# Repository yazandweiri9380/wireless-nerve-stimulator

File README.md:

# wireless-nerve-stimulator
Hardware designs, firmware, and supporting software for a compact wireless peripheral nerve stimulator with onboard inverse mapping.

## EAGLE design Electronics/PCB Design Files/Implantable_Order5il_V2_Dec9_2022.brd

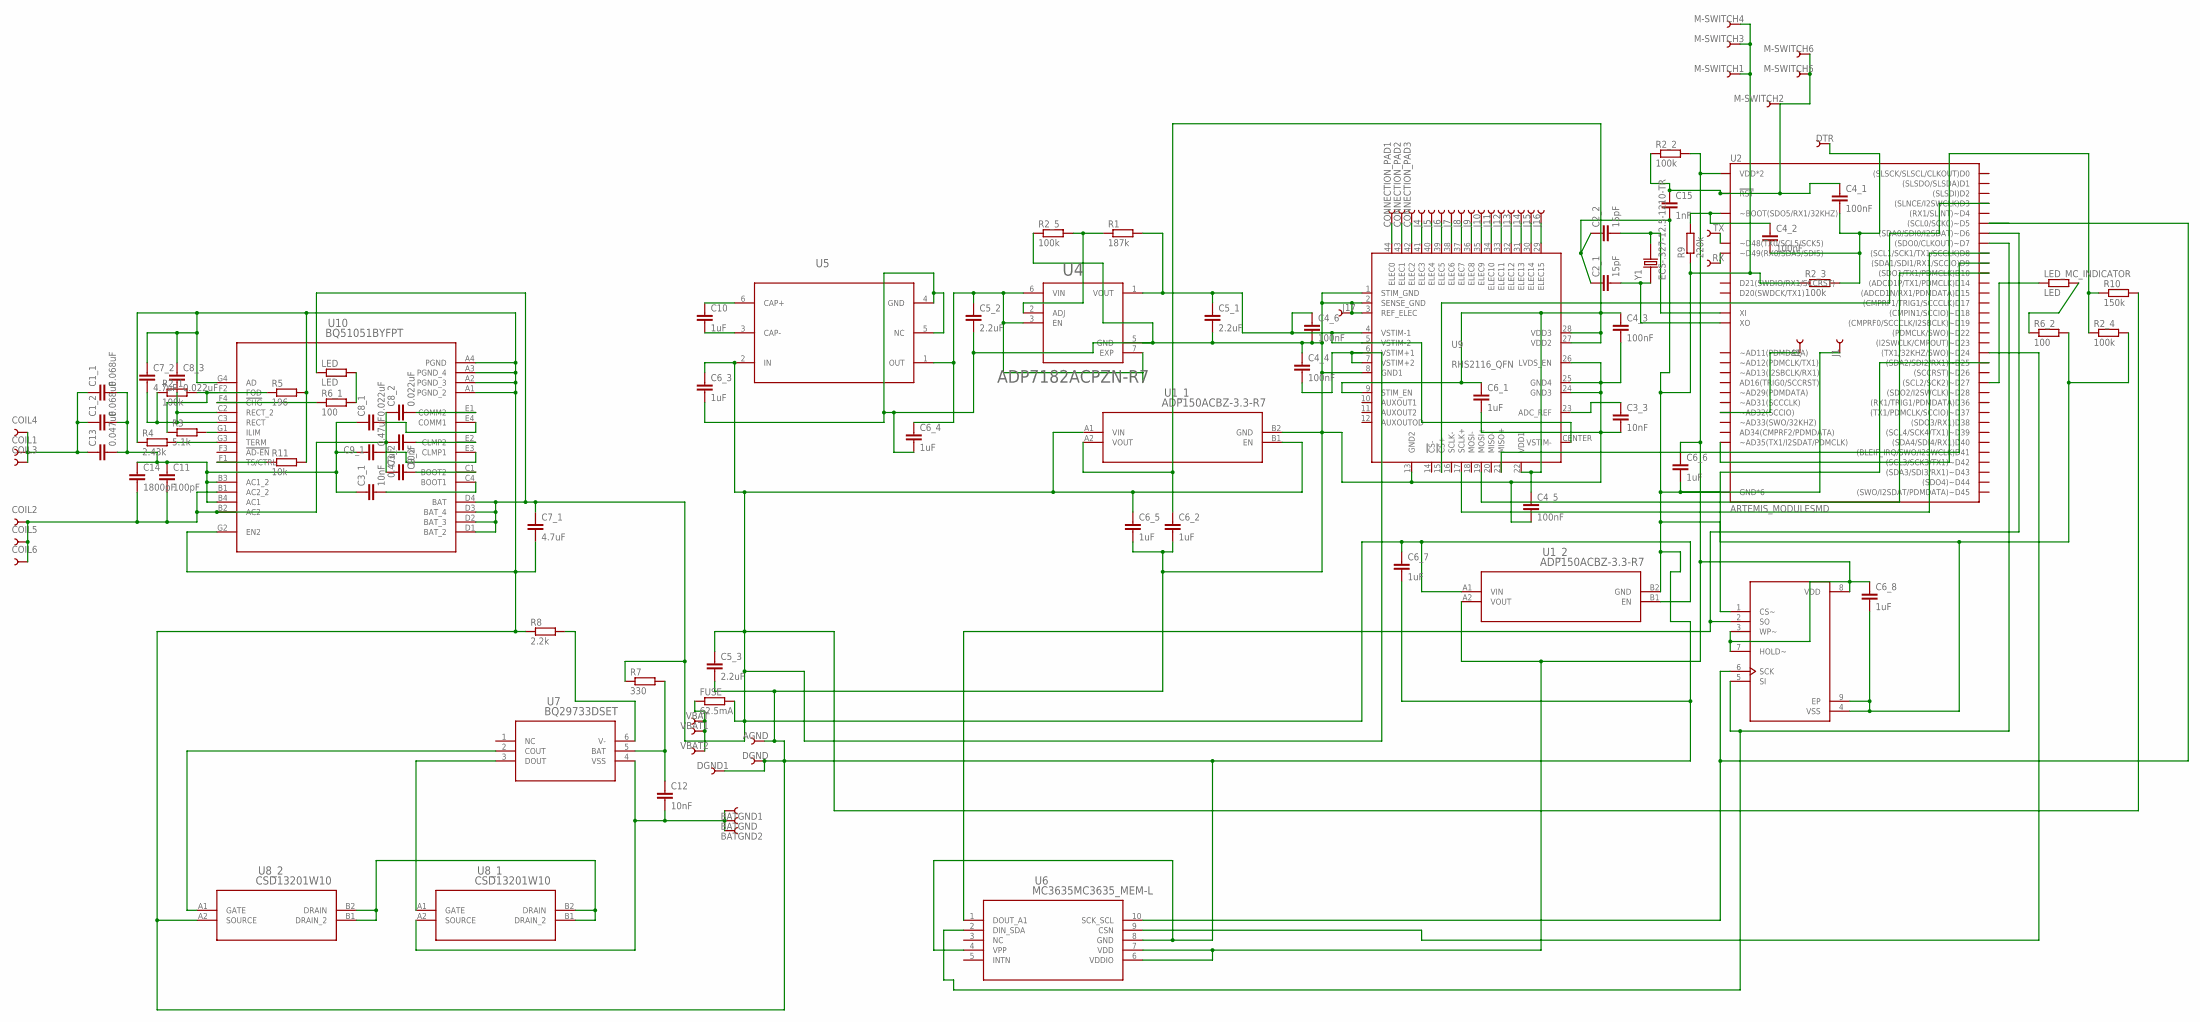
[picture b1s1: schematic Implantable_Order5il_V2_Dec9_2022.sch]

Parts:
AGND: PAD.4X.6; MODULE_PAD
BATGND, BATGND1, BATGND2: PAD.4X.6; MODULE_PAD
C1_1, C1_2: 0.068uF; C0402K; DIGIKEY 445-7346-1-ND
C2_1, C2_2: 15pF; C0201
C3_1, C3_2, C3_3: 10nF; C0201; DIGIKEY 587-5943-1-ND
C4_1, C4_2, C4_3, C4_4, C4_5, C4_6: 100nF; C0201
C5_1, C5_2, C5_3: 2.2uF; C0201; DIGIKEY 490-13227-1-ND
C6_1, C6_2, C6_3, C6_4, C6_5, C6_6, C6_7, C6_8: 1uF; C0201
C7_1, C7_2: 4.7uF; C0402K; DIGIKEY 1276-6836-1-ND
C8_1, C8_2, C8_3: 0.022uF; C0201; DIGIKEY 587-EMK063B7223KP-FCT-ND
C9_1, C9_2: 0.47uF; C0402K; DIGIKEY 587-3497-1-ND
C10: 1uF; C0402K
C11: 100pF; C0201; DIGIKEY 445-12105-1-ND
C12: 10nF; C0603; DIGIKEY C0603C103J3GACTU
C13: 0.047uF; C0201; DIGIKEY 445-13679-1-ND
C14: 1800pF; C0402K; DIGIKEY 399-C0402C182J5RAC7867CT-ND
C15: 1nF; C0201
COIL1, COIL2, COIL3, COIL4, COIL5, COIL6: PAD.4X.6; MODULE_PAD
CONNECTION_PAD1, CONNECTION_PAD2, CONNECTION_PAD3: PAD.4X.6; MODULE_PAD
DGND, DGND1: PAD.4X.6; MODULE_PAD
DTR: PAD.4X.6; MODULE_PAD
FUSE: 62.5mA; R0402; DIGIKEY F0402G0R06FNTR
J1, J2, J4, J5, J6, J7, J8, J9, J10, J11, J12, J13, J14, J15, J16, J17: PAD.4X.6; MODULE_PAD
LED: LED; R0201; DIGIKEY APG0603SEC-TT
LED_MC_INDICATOR: LED; R0201; DIGIKEY APG0603SEC-E-TT
M-SWITCH1, M-SWITCH2, M-SWITCH3, M-SWITCH4, M-SWITCH5, M-SWITCH6: PAD.4X.6; MODULE_PAD
R1: 187k; R0201; DIGIKEY 541-CRCW0201174KFNEDCT-ND
R2_1, R2_2, R2_3, R2_4: 100k; R0201
R2_5: 100k; R0201; DIGIKEY 541-2941-1-ND
R3: 5.1k; R0201
R4: 2.43k; R0201
R5: 196; R0201
R6_1, R6_2: 100; R0201
R7: 330; R0201
R8: 2.2k; R0201
R9: 220k; R0201
R10: 150k; R0201
R11: 10k; R0201
RX: PAD.4X.6; MODULE_PAD
TX: PAD.4X.6; MODULE_PAD
U1_1, U1_2: ADP150ACBZ-3.3-R7; CB_4_3_ADI
U2: ARTEMIS_MODULESMD; ARTEMIS_FP
U3: MB85RC64TAPN-G-AMEWE1; SON50P200X300X75-9N
U4: ADP7182ACPZN-R7; SON65P200X200X65-7N
U5: ADM8829ARTZ-REELRJ_6_ADI-L; RJ_6_ADI-L
U6: MC3635MC3635_MEM-L; MC3635_MEM-L
U7: BQ29733DSET; DSE6_TEX
U8_1, U8_2: CSD13201W10; YZB4_TEX
U9: RHS2116_QFN; QFN44_7_X_7
U10: BQ51051BYFPT; YFP28
VBAT, VBAT1, VBAT2: PAD.4X.6; MODULE_PAD
Y1: ECS-.327-12.5-1210-TR; XTAL_ECS-.327-12.5-1210-TR

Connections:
BG: BATGND.1, BATGND1.1, BATGND2.1, C12.2, U7.4 (VSS), U8_1.A2 (SOURCE)
BOOT: C4_2.1, R9.2, U2.BOOT (~BOOT(SDO5/RX1/32KHZ))
CS2: U2.~D25 ((SDA2/SDI2/RX1)~D25), U3.1 (CS~)
DRT: C4_1.2, C4_2.2, DTR.1, R2_3.2
G: AGND.1, C2_1.1, C2_2.1, C3_3.2, C4_3.2, C4_4.1, C4_5.2, C4_6.2, C5_1.2, C5_2.2, C5_3.2, C6_1.2, C6_2.2, C6_3.2, C6_4.2, C6_5.2, C6_6.2, C6_7.2, C6_8.2, C7_1.2, C7_2.1, C8_3.1, C15.2, DGND.1, DGND1.1, J1.1, J17.1, M-SWITCH1.1, M-SWITCH3.1, M-SWITCH4.1, R2_3.1, R2_4.2, R2_5.1, R4.1, R5.2, R6_2.2, R8.1, R9.1, R11.2, U1_1.B2 (GND), U1_2.B2 (GND), U2.GND@1 (GND*6), U2.GND@22 (GND*6), U2.GND@38 (GND*6), U2.GND@39 (GND*6), U2.GND@47 (GND*6), U2.GND@59 (GND*6), U3.4 (VSS), U3.9 (EP), U4.5 (GND), U5.4 (GND), U5.5 (NC), U6.4 (VPP), U6.8 (GND), U8_2.A2 (SOURCE), U9.1 (STIM_GND), U9.2 (SENSE_GND), U9.3 (REF_ELEC), U9.8 (GND1), U9.13 (GND2), U9.24 (GND3), U9.25 (GND4), U9.26 (LVDS_EN), U10.A1 (PGND_2), U10.A2 (PGND_3), U10.A3 (PGND_4), U10.A4 (PGND), U10.G2 (EN2), U10.G4 (AD)
MISO: U2.D9 ((SDA1/SDI1/RX1/SCCIO)D9), U9.21 (MISO+)
MOSI: U2.D10 ((SDO1/TX1/PDMCLK)D10), U9.19 (MOSI+)
MS+: C4_1.1, C15.1, M-SWITCH2.1, M-SWITCH5.1, M-SWITCH6.1, R2_2.1, U2.~RST (!RST)
unnamed: J6.1, U9.39 (ELEC5)
unnamed: J16.1, U9.29 (ELEC15)
unnamed: CONNECTION_PAD1.1, U9.44 (ELEC0)
unnamed: CONNECTION_PAD2.1, U9.43 (ELEC1)
unnamed: CONNECTION_PAD3.1, U9.42 (ELEC2)
unnamed: J4.1, U9.41 (ELEC3)
unnamed: J5.1, U9.40 (ELEC4)
unnamed: J7.1, U9.38 (ELEC6)
unnamed: J8.1, U9.37 (ELEC7)
unnamed: J9.1, U9.36 (ELEC8)
unnamed: J10.1, U9.35 (ELEC9)
unnamed: J11.1, U9.34 (ELEC10)
unnamed: J12.1, U9.33 (ELEC11)
unnamed: J13.1, U9.32 (ELEC12)
unnamed: J14.1, U9.31 (ELEC13)
unnamed: J15.1, U9.30 (ELEC14)
unnamed: R2_4.1, R10.1, U2.~AD35 (~AD35(TX1/I2SDAT/PDMCLK))
unnamed: C2_1.2, U2.XO, Y1.1 (IN/OUT)
unnamed: C12.1, R7.2, U7.5 (BAT)
unnamed: LED_MC_INDICATOR.1, U2.~D27 ((SCL2/SCK2)~D27)
unnamed: FUSE.1, VBAT.1, VBAT1.1, VBAT2.1
unnamed: C4_6.1, C5_1.1, R1.2, U4.1 (VOUT), U9.4 (VSTIM-1), U9.5 (VSTIM-2), U9.CENTER (VSTIM-)
unnamed: U2.D3 ((SLNCE/I2SWCLK)D3), U9.15 (!CS!+)
unnamed: C2_2.2, U2.XI, Y1.2 (OUT/IN)
unnamed: U7.3 (DOUT), U8_1.A1 (GATE)
unnamed: J2.1, U2.~AD32 (~AD32(SCCIO))
unnamed: C5_2.1, C6_4.1, U4.3 (EN), U4.6 (VIN), U4.7 (EXP), U5.1 (OUT)
unnamed: C3_3.1, U9.23 (ADC_REF)
unnamed: R1.1, R2_5.2, U4.2 (ADJ)
unnamed: U7.2 (COUT), U8_2.A1 (GATE)
unnamed: TX.1, U2.TXO-0 (~D48(TX0/SCL5/SCK5))
unnamed: C10.1, U5.6 (CAP+)
unnamed: C10.2, U5.3 (CAP-)
unnamed: C1_1.1, C1_2.1, C13.1, COIL1.1, COIL3.1, COIL4.1
unnamed: C8_2.2, U10.E1 (COMM2)
unnamed: U8_1.B1 (DRAIN_2), U8_1.B2 (DRAIN), U8_2.B1 (DRAIN_2), U8_2.B2 (DRAIN)
unnamed: R8.2, U7.6 (V-)
unnamed: C7_2.2, C8_3.2, R2_1.1, U10.C2 (RECT_2), U10.C3 (RECT)
unnamed: C3_1.2, U10.C4 (BOOT1)
unnamed: C9_1.2, U10.E3 (CLMP1)
unnamed: C8_1.2, U10.E4 (COMM1)
unnamed: R2_1.2, R3.1, R5.1, U10.F2 (FOD)
unnamed: C1_1.2, C1_2.2, C3_1.1, C8_1.1, C9_1.1, C11.1, C13.2, C14.1, U10.B3 (AC1_2), U10.B4 (AC1)
unnamed: C9_2.1, U10.E2 (CLMP2)
unnamed: C3_2.2, U10.C1 (BOOT2)
unnamed: C3_2.1, C8_2.1, C9_2.2, C11.2, C14.2, COIL2.1, COIL5.1, COIL6.1, U10.B1 (AC2_2), U10.B2 (AC2)
unnamed: R11.1, U10.F1 (TS/CTRL)
unnamed: R3.2, U10.G1 (ILIM)
unnamed: R4.2, U10.G3 (TERM)
unnamed: R6_1.1, U10.F4 (!CHG)
unnamed: LED.2, R6_1.2
unnamed: U2.~D24 ((TX1/32KHZ/SWO)~D24), U6.9 (CSN)
unnamed: RX.1, U2.RXI-0 (~D49(RX0/SDA5/SDI5))
unnamed: LED_MC_INDICATOR.2, R6_2.1
SCK: U2.D8 ((SCL1/SCK1/TX1/SCCLK)D8), U9.17 (SCLK+)
SCK2: U2.~D5 ((SCL0/SCK0)~D5), U3.6 (SCK), U6.10 (SCK_SCL)
SI: U2.D7 ((SDO0/CLKOUT)~D7), U3.5 (SI), U6.2 (DIN_SDA)
SO: U2.~D6 ((SDA0/SDI0/I2SDAT)~D6), U3.2 (SO), U6.1 (DOUT_A1)
VBAT: C4_4.2, C5_3.1, C6_3.1, C6_5.1, C6_7.1, C7_1.1, FUSE.2, LED.1, R7.1, R10.2, U1_1.A1 (VIN), U1_1.B1 (EN), U1_2.A1 (VIN), U1_2.B1 (EN), U5.2 (IN), U9.6 (VSTIM+1), U9.7 (VSTIM+2), U10.D1 (BAT_2), U10.D2 (BAT_3), U10.D3 (BAT_4), U10.D4 (BAT)
V_INTAN: C4_3.1, C4_5.1, C6_1.1, C6_2.1, U1_1.A2 (VOUT), U9.9 (STIM_EN), U9.22 (VDD1), U9.27 (VDD2), U9.28 (VDD3)
V_MC: C6_6.1, C6_8.1, R2_2.2, U1_2.A2 (VOUT), U2.VDD@36 (VDD*2), U2.VDD@37 (VDD*2), U3.3 (WP~), U3.7 (HOLD~), U3.8 (VDD), U6.6 (VDDIO), U6.7 (VDD)

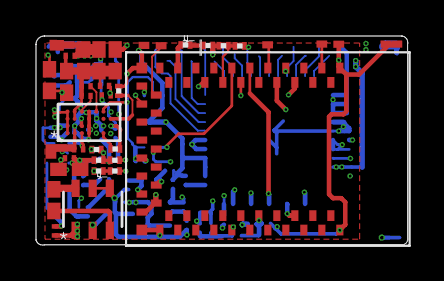
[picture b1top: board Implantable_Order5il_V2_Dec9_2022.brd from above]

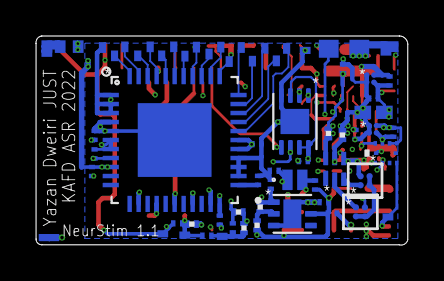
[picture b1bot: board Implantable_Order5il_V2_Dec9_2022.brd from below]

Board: 4 copper layers, 20.7 x 11.6 mm, 112 parts (70 on the bottom side), 69 nets.

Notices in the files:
parts and their libraries:
SparkFun-IC-Microcontroller: Licensing: Creative Commons ShareAlike 4.0 International - https://creativecommons.org/licenses/by-sa/4.0
COPYRIGHT: Copyright (C) 2022 Ultra Librarian. All rights reserved.
